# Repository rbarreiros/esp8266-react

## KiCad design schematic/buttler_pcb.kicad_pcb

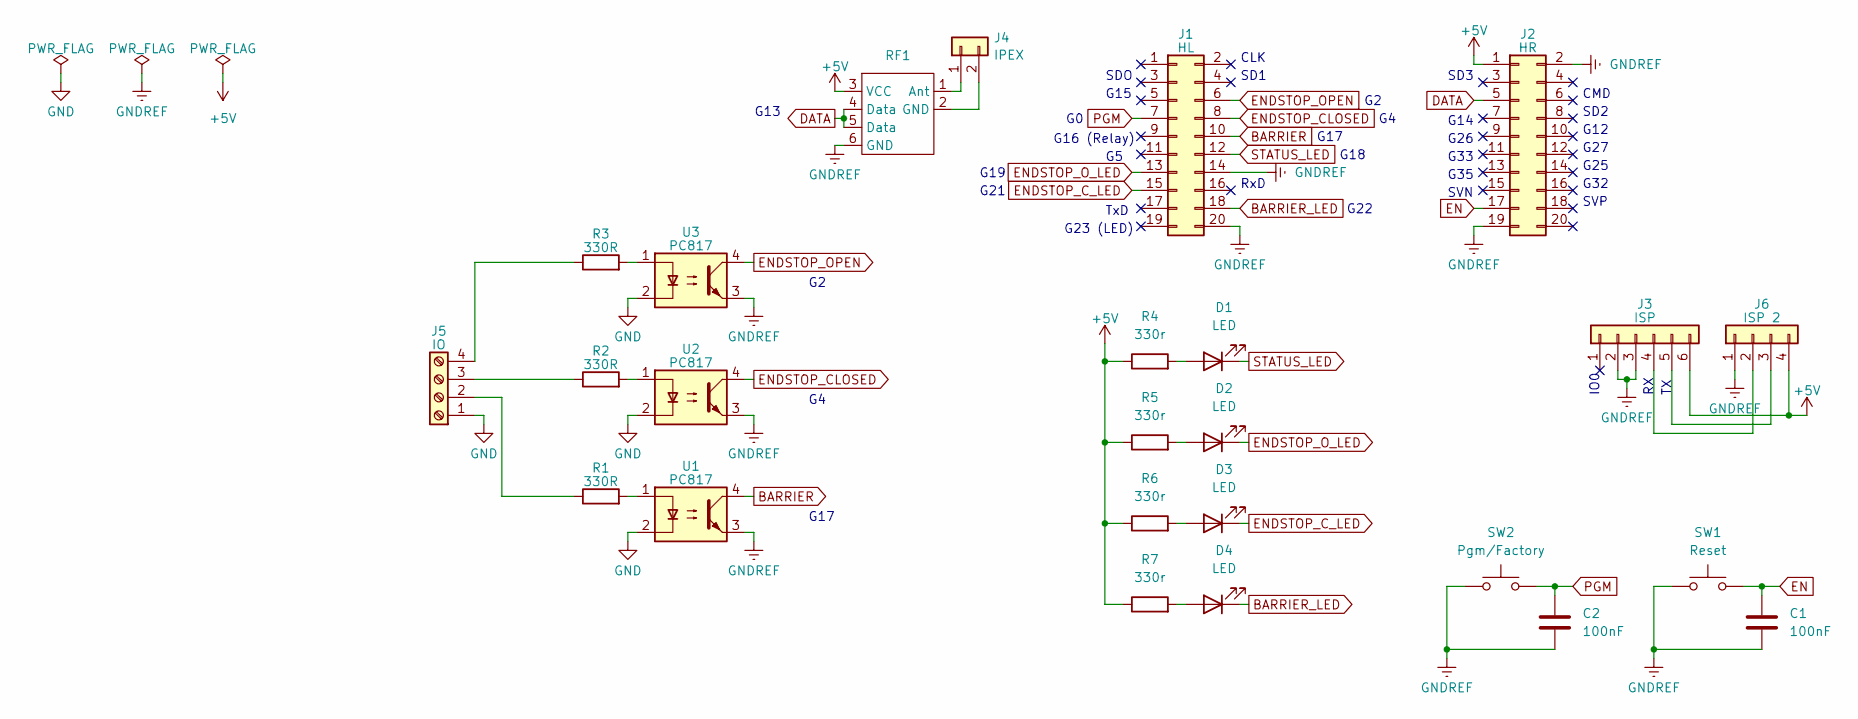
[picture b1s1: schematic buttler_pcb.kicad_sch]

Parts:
C1, C2: 100nF; C_0402_1005Metric
D1, D2, D3, D4: LED; LED_0603_1608Metric
J1: HL; PinHeader_2x10_P2.54mm_Vertical
J2: HR; PinHeader_2x10_P2.54mm_Vertical
J3: ISP; PinHeader_1x06_P2.54mm_Vertical
J4: IPEX; IPEX_20279-001E-03
J5: IO; TerminalBlock_bornier-4_P5.08mm
J6: ISP 2; PinHeader_1x04_P2.54mm_Vertical
R1, R2, R3: 330R; R_0603_1608Metric
R4, R5, R6, R7: 330r; R_0603_1608Metric
RF1: RXB12
SW1: Reset; SW_SPST_TL3342
SW2: Pgm/Factory; SW_SPST_TL3342
U1, U2, U3: PC817; OPTO-SMD4

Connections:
+5V: J2.1, J3.6, J6.4, R4.1, R5.1, R6.1, R7.1, RF1.3 (VCC)
BARRIER: J1.10, U1.4
BARRIER_LED: D4.1 (K), J1.18
DATA: J2.5, RF1.4 (Data), RF1.5 (Data)
EN: C1.1, J2.17, SW1.2
ENDSTOP_CLOSED: J1.8, U2.4
ENDSTOP_C_LED: D3.1 (K), J1.15
ENDSTOP_OPEN: J1.6, U3.4
ENDSTOP_O_LED: D2.1 (K), J1.13
GND: J5.1, U1.2, U2.2, U3.2
GNDREF: C1.2, C2.2, J1.14, J1.20, J2.2, J2.19, J3.2, J3.3, J6.1, RF1.6 (GND), SW1.1, SW2.1, U1.3, U2.3, U3.3
unnamed: D1.2 (A), R4.2
unnamed: D2.2 (A), R5.2
unnamed: D3.2 (A), R6.2
unnamed: D4.2 (A), R7.2
unnamed: J3.4, J6.2
unnamed: J3.5, J6.3
unnamed: J4.1, RF1.1 (Ant)
unnamed: J4.2, RF1.2 (GND)
unnamed: J5.2, R1.1
unnamed: J5.3, R2.1
unnamed: J5.4, R3.1
unnamed: R1.2, U1.1
unnamed: R2.2, U2.1
unnamed: R3.2, U3.1
PGM: C2.1, J1.7, SW2.2
STATUS_LED: D1.1 (K), J1.12

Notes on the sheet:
G17
SDO
G15
G25
G27
SVP
CMD
G32
SD3
G19
G26
G16 (Relay)
TxD
SD1
G22
G33
G13
G12
G35
SVN
G14
G23 (LED)
G21
IO0
CLK
G18
SD2
RxD

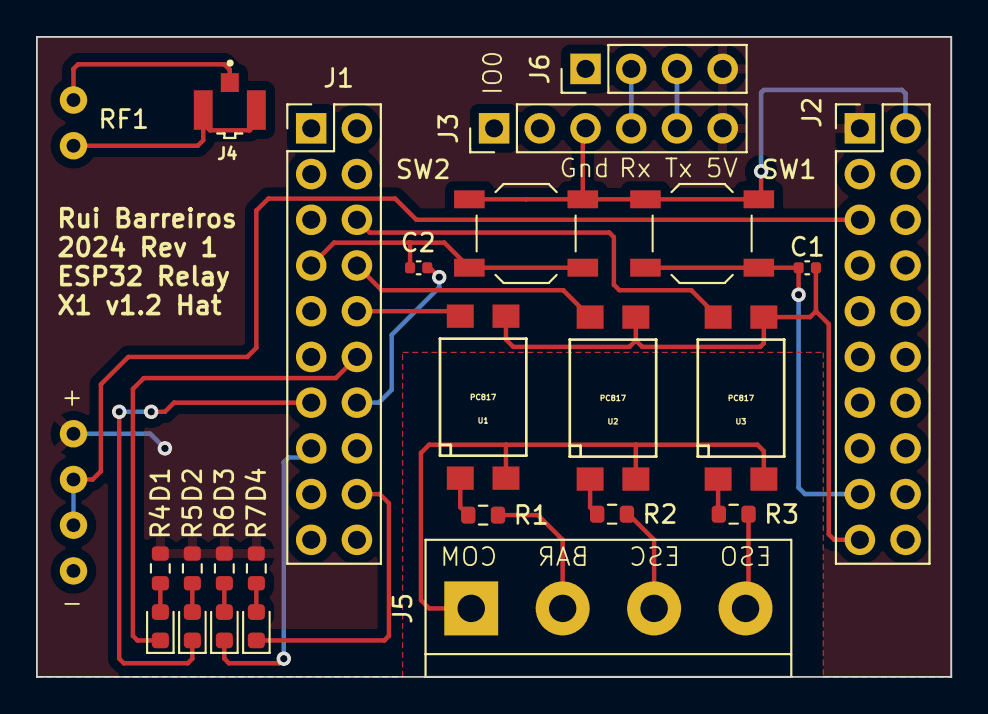
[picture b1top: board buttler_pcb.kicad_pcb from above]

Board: 2 copper layers, 50.8 x 35.6 mm, 25 parts (0 on the bottom side), 27 nets.

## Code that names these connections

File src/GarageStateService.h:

#ifndef _GARAGESTATESERVICE_H_
#define _GARAGESTATESERVICE_H_

#include <MqttPubSub.h>
#include <StatefulService.h>
#include <WebSocketTxRx.h>

#include "RFRemoteController.h"

#define GARAGE_STATE_SOCKET_PATH "/ws/garageState"

#define DEFAULT_RELAY_STATE false

#define RELAY_PIN 16
#define RELAY_ON HIGH
#define RELAY_OFF LOW

#define OFF_STATE "OFF"
#define ON_STATE "ON"

// N.C endstops
// pull up to 5v

#define ENDSTOP_CLOSED_PIN 4
#define ENDSTOP_CLOSED_ON LOW
#define ENDSTOP_CLOSED_OFF HIGH
#define ENDSTOP_OPEN_PIN 2
#define ENDSTOP_OPEN_ON LOW
#define ENDSTOP_OPEN_OFF HIGH

#define BARRIER_PIN 17
#define BARRIER_ON LOW
#define BARRIER_OFF HIGH

// HA relay as a switch
// HA status as sensor
// HA endstops as binary_sensor

class GarageState
{
   public:
    enum GarageStatus_t
    {
        STATUS_ERROR = 0,
        STATUS_CLOSED,
        STATUS_OPENING,
        STATUS_CLOSING,
        STATUS_OPEN
    };

    static const String m_statusString[5];

    static String stateToString(GarageStatus_t state) 
        { return m_statusString[static_cast<uint8_t>(state)]; }

    bool relayOn;
    GarageStatus_t status = STATUS_ERROR;  // current status of garage door
    bool endstopClosed = false;            // status of close endstop
    bool endstopOpen = false;              // status of open endstop
    bool barrierTriggered = false;          // status of IR barrier

    static void read(GarageState& settings, JsonObject& root)
    {
        root["relay_on"] = settings.relayOn;
        root["endstop_closed"] = settings.endstopClosed;
        root["endstop_open"] = settings.endstopOpen;
        root["barrier_triggered"] = settings.barrierTriggered;
        root["status"] = settings.status;
    }

    static StateUpdateResult update(JsonObject& root, GarageState& garageState)
    {
        StateUpdateResult changed = StateUpdateResult::UNCHANGED;

        bool relayNewState = root["relay_on"] | DEFAULT_RELAY_STATE;

        if (garageState.relayOn != relayNewState)
        {
            garageState.relayOn = relayNewState;
            changed = StateUpdateResult::CHANGED;
        }

        return changed;
    }

    static void haRelayRead(GarageState& settings, JsonObject& root)
    {
        root["state"] = settings.relayOn ? ON_STATE : OFF_STATE;
        
        Serial.printf("Setting state to %s.\r\n", root["state"].as<const char*>());
    }

    static StateUpdateResult haRelayUpdate(JsonObject& root,
                                      GarageState& garageState)
    {
        String state = root["state"];
        bool newState = false;

        if(state.equals(ON_STATE))
            newState = true;
        else if(!state.equals(OFF_STATE))
            return StateUpdateResult::ERROR;


        if(garageState.relayOn != newState)
        {
            garageState.relayOn = newState;
            return StateUpdateResult::CHANGED;
        }

        return StateUpdateResult::UNCHANGED;
    }

    static void haStatusRead(GarageState& settings, JsonObject& root)
    {
        root["state"] = GarageState::stateToString(settings.status);
    }

    static void haEndstopOpenRead(GarageState& settings, JsonObject& root)
    {
        root["state"] = settings.endstopOpen ? ON_STATE : OFF_STATE;
    }

    static void haEndstopClosedRead(GarageState& settings, JsonObject& root)
    {
        root["state"] = settings.endstopClosed ? ON_STATE : OFF_STATE;
    }

    static void haBarrierTriggeredRead(GarageState& settings, JsonObject& root)
    {
        root["state"] = settings.barrierTriggered ? ON_STATE : OFF_STATE;
    }

    static StateUpdateResult haDummyUpdate(JsonObject& root,
                                      GarageState& GarageState)
    {
        return StateUpdateResult::UNCHANGED;
    }
};

class GarageStateService : public StatefulService<GarageState>
{
public:
    GarageStateService(AsyncWebServer* server, SecurityManager* securityManager, espMqttClientAsync* mqttClient);
    void begin();
    void loop();

    void setRelayAutoOff(bool off) { m_relayAutoOff = off; }
    void setRelayOnTimer(unsigned long timer) { m_relayOnTimer = timer; }
    bool getRelayAutoOff() { return m_relayAutoOff; }
    unsigned long getRelayOnTimer() { return m_relayOnTimer; }

private:
    WebSocketTxRxDelta<GarageState> m_webSocket;
    espMqttClientAsync* m_mqttClient;
    
    // Consolidated MQTT - single topic for all garage data
    MqttPubSub<GarageState> m_mqttConsolidatedPubSub;
    
    // Individual HA topics for backward compatibility (can be removed later)
    MqttPubSub<GarageState> m_mqttBarrierPubSub;
    MqttPubSub<GarageState> m_mqttEndstopClosedPubSub;
    MqttPubSub<GarageState> m_mqttEndstopOpenPubSub;
    MqttPubSub<GarageState> m_mqttStatusPubSub;
    MqttPubSub<GarageState> m_mqttRelayPubSub;

    GarageState::GarageStatus_t m_lastEsState = GarageState::STATUS_ERROR;
    bool m_relayAutoOff;
    unsigned long m_relayOnTimer;

    void registerConfig();
    void onConfigUpdate();
    void updateEndstops();
    void getDevice(JsonObject& dev);
    void registerRelay();
    void registerStatus();
    void registerEndstopOpen();
    void registerEndstopClosed();
    void registerBarrier();
    void registerConsolidatedTopic();

    // Consolidated MQTT payload readers
    static void consolidatedRead(GarageState& state, JsonObject& root);
    static StateUpdateResult consolidatedUpdate(JsonObject& root, GarageState& state);
};

#endif

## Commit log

2024-07-29 Updated arduinojson to latest, moved from async-mqtt-client to espMqttClient. Lots of code refactoring and formatting. Added relay settings and service to be used with rc-switch later on.
2024-07-30 Fixed more errors due to upgrades. Started VUE implementation.
2024-07-30 Repo sync
2024-07-31 Many fixes....
2024-08-01 Fixes. Added support for custom led and factory reset button. Added support for configuring auto relay turn off and time
2024-08-02 Implemented some new stuff in vue
2024-08-08 Lots of new stuff. Lots of new bugs.... We need to fix fs persistence, even on esp8266react framework, there are some racing conditions on reading/writing to filesystem. Need to separate what is sett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
2024-08-10 Some refactoring, state and settings split (settings save to filesystem, states never). Fixed Garage(state/settings) in interface.
2024-08-12 Saga continues, sorting out the interface to crud remotes, hate web stuff, hate react and javascript... oh well.
2024-08-13 Refactored everything from string to char* and still the bug persists and finally found it. Race condition between littlefs using flash and interrupt trying to call functions stored in flash, bang cr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
2024-08-13 quick hack to fix the race condition created by rf433recv interrupt, it accesses functions not in iram (several) during the int processing thus when littlefs is accessing filesystem, all hell breaks 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
2024-08-16 repo syncy
2024-08-26 Preliminary alpha, everything seems to be working - Implemented barrier monitoring and mqtt states - Removed MQTT settings react pages, don't think they make sense
2024-08-26 Added support for pairing through MQTT, and fixed couple of bugs
2024-09-01 Added schematic for buttle hat Working on getting tasks working
2025-07-26 Main optimized and static init moved to setup so it's started properly and in order.
2025-07-26 In a working state and most of bad bugs fixed.
